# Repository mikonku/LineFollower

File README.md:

# linefollowerPRC

This is my project to build linefollower robot with PID control and several control which used usually in PRC robotic training at my college.

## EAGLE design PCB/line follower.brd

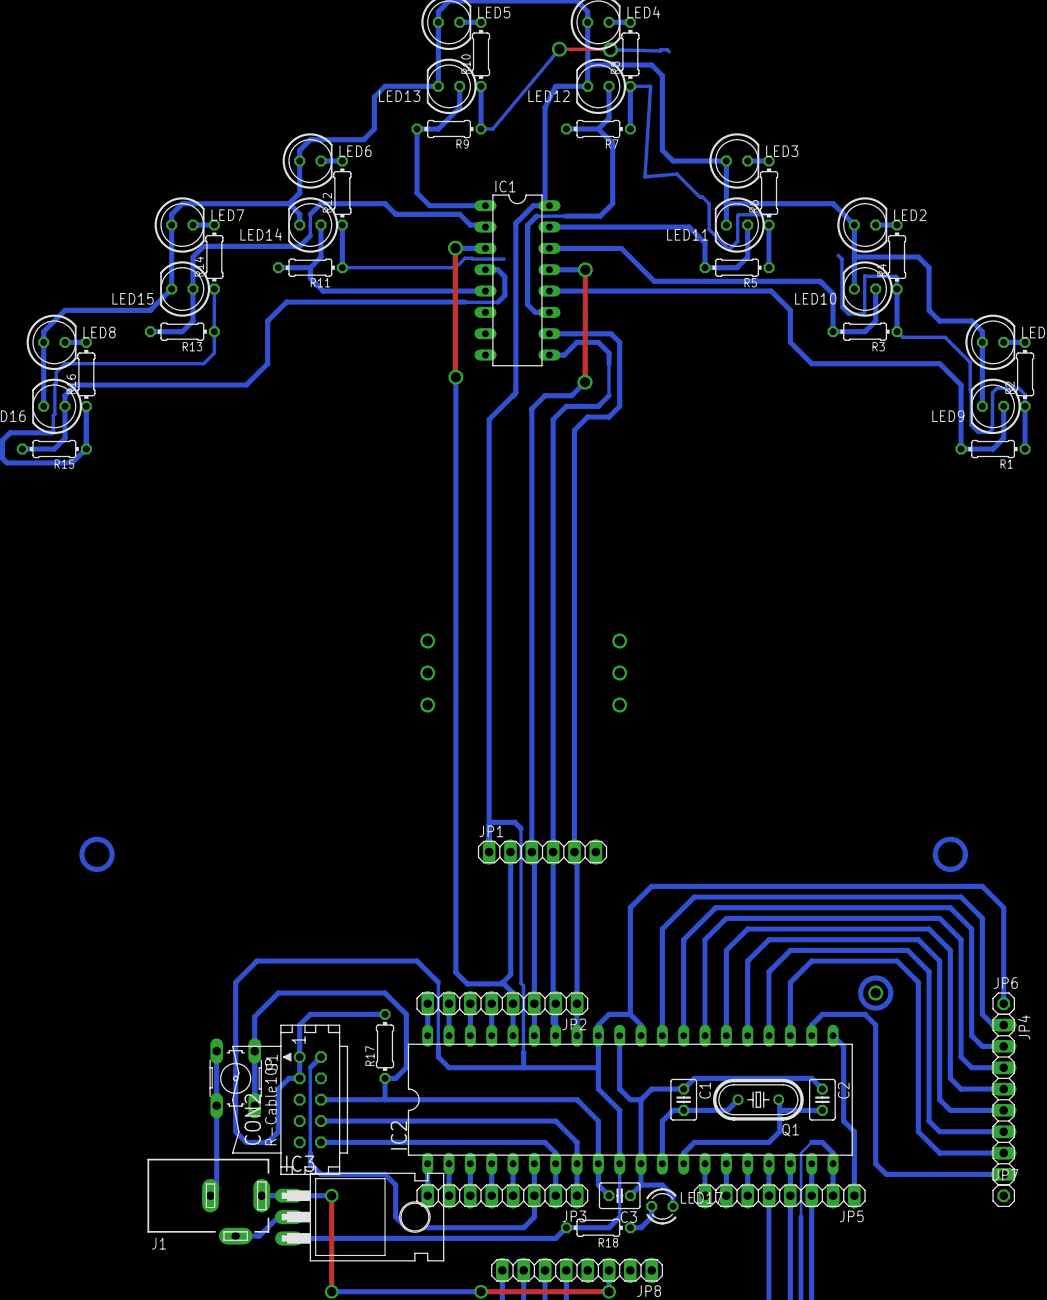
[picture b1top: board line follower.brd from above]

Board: 2 copper layers, 53 parts (0 on the bottom side), 55 nets.

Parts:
C1, C2, C3: C025-030X050
CON2: CON10L
IC1: 4052N; DIL16
IC2: MEGA32-P; DIL40
IC3: 7805T; TO220H
J1: DCJ0303
JP1: 1X06
JP2, JP3, JP4, JP5, JP8: 1X08
JP6, JP7: 1X01
LED1, LED2, LED3, LED4, LED5, LED6, LED7, LED8, LED9, LED10, LED11, LED12, LED13, LED14, LED15, LED16: LED5MM
LED17: LED3MM
Q1: HC49U-V
R1, R2, R3, R4, R5, R6, R7, R8, R9, R10, R11, R12, R13, R14, R15, R16, R17, R18: 0204/7
S1: B3F-10XX

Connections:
+12V: IC3.1, J1.1, JP8.3
GND: C1.1, C2.1, C3.1, CON2.7, CON2.9, IC1.6, IC1.8, IC2.11, IC2.31, IC3.2, J1.2, J1.3, JP1.6, JP7.1, JP8.1, JP8.4, LED17.K, R1.1, R2.1, R3.1, R4.1, R5.1, R6.1, R7.1, R8.1, R9.1, R10.1, R11.1, R12.1, R13.1, R14.1, R15.1, R16.1, S1.3, S1.4
unnamed: LED1.K, R2.2
unnamed: IC1.12, LED9.A, R1.2
unnamed: IC1.9, IC2.34, JP1.4, JP2.2
unnamed: IC2.37, JP2.5
unnamed: LED2.K, R4.2
unnamed: IC1.14, LED10.A, R3.2
unnamed: LED3.K, R6.2
unnamed: IC1.15, LED11.A, R5.2
unnamed: LED4.K, R8.2
unnamed: IC1.11, LED12.A, R7.2
unnamed: LED5.K, R10.2
unnamed: IC1.3, IC2.36, JP1.2, JP2.4
unnamed: LED6.K, R12.2
unnamed: IC1.13, IC2.35, JP1.3, JP2.3
unnamed: LED7.K, R14.2
unnamed: LED8.K, R16.2
unnamed: IC2.19, JP5.3, JP8.8
unnamed: C1.2, IC2.12, Q1.2
unnamed: C2.2, IC2.13, Q1.1
unnamed: CON2.8, IC2.8, JP3.1
unnamed: C3.2, CON2.6, IC2.9, R17.1, S1.1, S1.2
unnamed: LED17.A, R18.1
unnamed: CON2.2, IC2.6, JP3.3
unnamed: CON2.10, IC2.7, JP3.2
unnamed: IC1.10, IC2.33, JP1.5, JP2.1
unnamed: IC2.38, JP2.6
unnamed: IC2.39, JP2.7
unnamed: IC2.40, JP2.8
unnamed: IC2.5, JP3.4
unnamed: IC2.4, JP3.5
unnamed: IC2.3, JP3.6
unnamed: IC2.2, JP3.7
unnamed: IC2.1, JP3.8
unnamed: IC2.29, JP4.1
unnamed: IC1.4, LED16.A, R15.2
unnamed: IC1.2, LED15.A, R13.2
unnamed: IC1.5, LED14.A, R11.2
unnamed: IC1.1, LED13.A, R9.2
unnamed: IC2.28, JP4.2
unnamed: IC2.27, JP4.3
unnamed: IC2.26, JP4.4
unnamed: IC2.25, JP4.5
unnamed: IC2.24, JP4.6
unnamed: IC2.23, JP4.7
unnamed: IC2.22, JP4.8
unnamed: IC2.21, JP5.1
unnamed: IC2.20, JP5.2, JP8.7
unnamed: IC2.18, JP5.4, JP8.6
unnamed: IC2.17, JP5.5, JP8.5
unnamed: IC2.16, JP5.6
unnamed: IC2.15, JP5.7
unnamed: IC2.14, JP5.8
VCC: CON2.1, CON2.3, IC1.16, IC2.10, IC2.30, IC2.32, IC3.3, JP1.1, JP6.1, LED1.A, LED2.A, LED3.A, LED4.A, LED5.A, LED6.A, LED7.A, LED8.A, LED9.K, LED10.K, LED11.K, LED12.K, LED13.K, LED14.K, LED15.K, LED16.K, R17.2, R18.2
